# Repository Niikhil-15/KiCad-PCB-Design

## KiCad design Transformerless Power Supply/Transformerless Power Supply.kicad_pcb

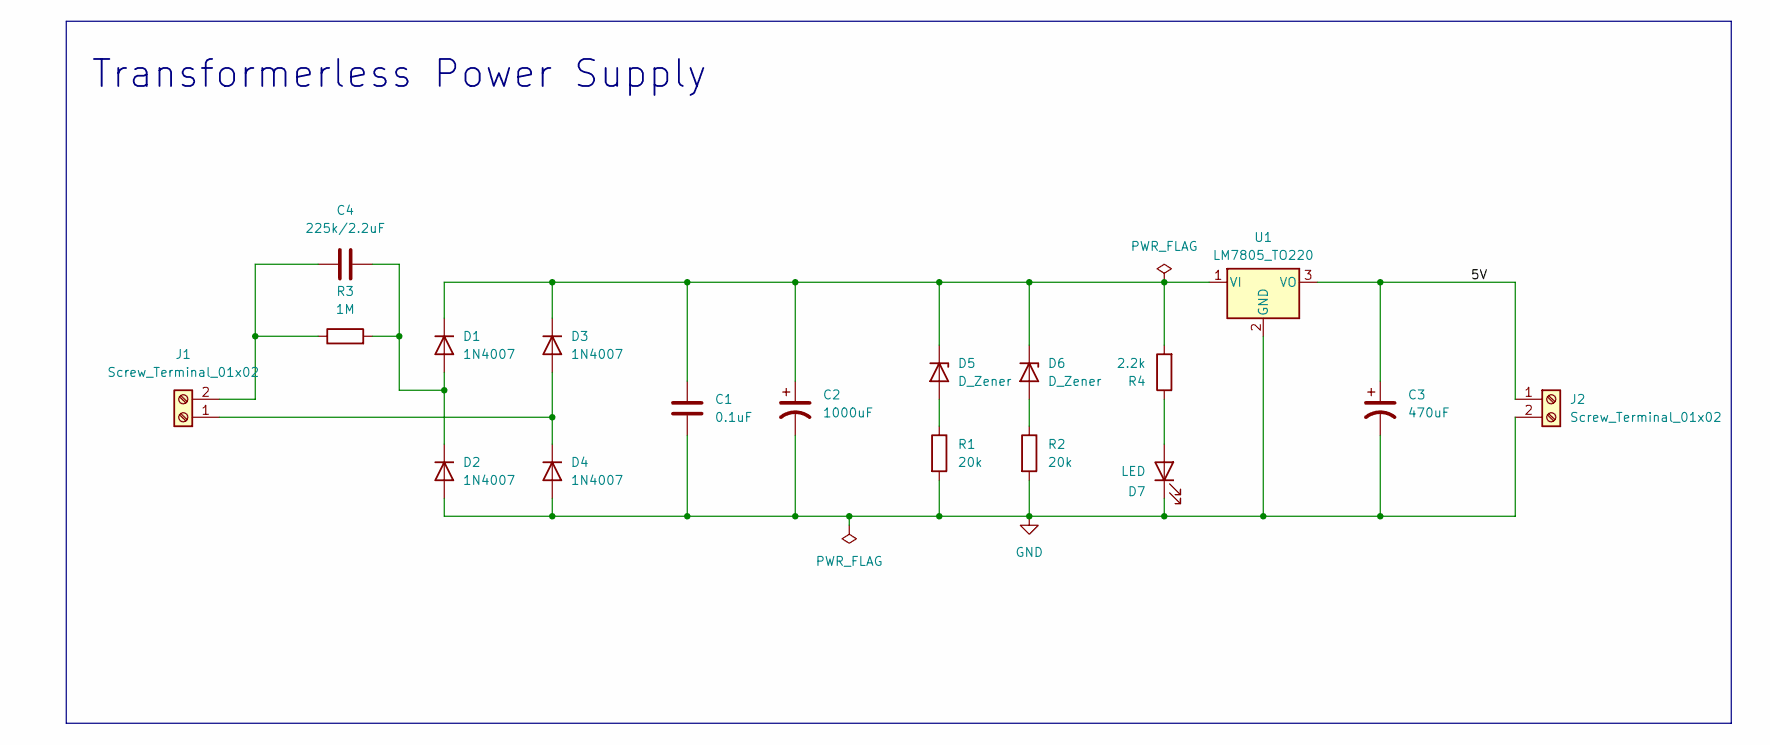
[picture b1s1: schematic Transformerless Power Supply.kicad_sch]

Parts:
C1: 0.1uF; C_Disc_D5.0mm_W2.5mm_P5.00mm
C2: 1000uF; CP_Radial_D12.5mm_P7.50mm
C3: 470uF; CP_Radial_D10.0mm_P2.50mm
C4: 225k/2.2uF; C_Rect_L9.0mm_W3.3mm_P7.50mm_MKT
D1, D2, D3, D4: 1N4007; D_DO-41_SOD81_P10.16mm_Horizontal
D5, D6: D_Zener; D_DO-34_SOD68_P7.62mm_Horizontal
D7: LED; LED_D5.0mm
J1, J2: Screw_Terminal_01x02; TerminalBlock_MaiXu_MX126-5.0-02P_1x02_P5.00mm
R1, R2: 20k; R_Axial_DIN0207_L6.3mm_D2.5mm_P7.62mm_Horizontal
R3: 1M; R_Axial_DIN0207_L6.3mm_D2.5mm_P7.62mm_Horizontal
R4: 2.2k; R_Axial_DIN0207_L6.3mm_D2.5mm_P7.62mm_Horizontal
U1: LM7805_TO220; TO-220-3_Vertical

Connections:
/5V: C3.1, J2.1, U1.3 (VO)
GND: C1.2, C2.2, C3.2, D2.2 (A), D4.2 (A), D7.1 (K), J2.2, R1.2, R2.2, U1.2 (GND)
unnamed: C4.2, D1.2 (A), D2.1 (K), R3.2
unnamed: C1.1, C2.1, D1.1 (K), D3.1 (K), D5.1 (K), D6.1 (K), R4.2, U1.1 (VI)
unnamed: D3.2 (A), D4.1 (K), J1.1
unnamed: D5.2 (A), R1.1
unnamed: D6.2 (A), R2.1
unnamed: D7.2 (A), R4.1
unnamed: C4.1, J1.2, R3.1

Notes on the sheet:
Transformerless Power Supply

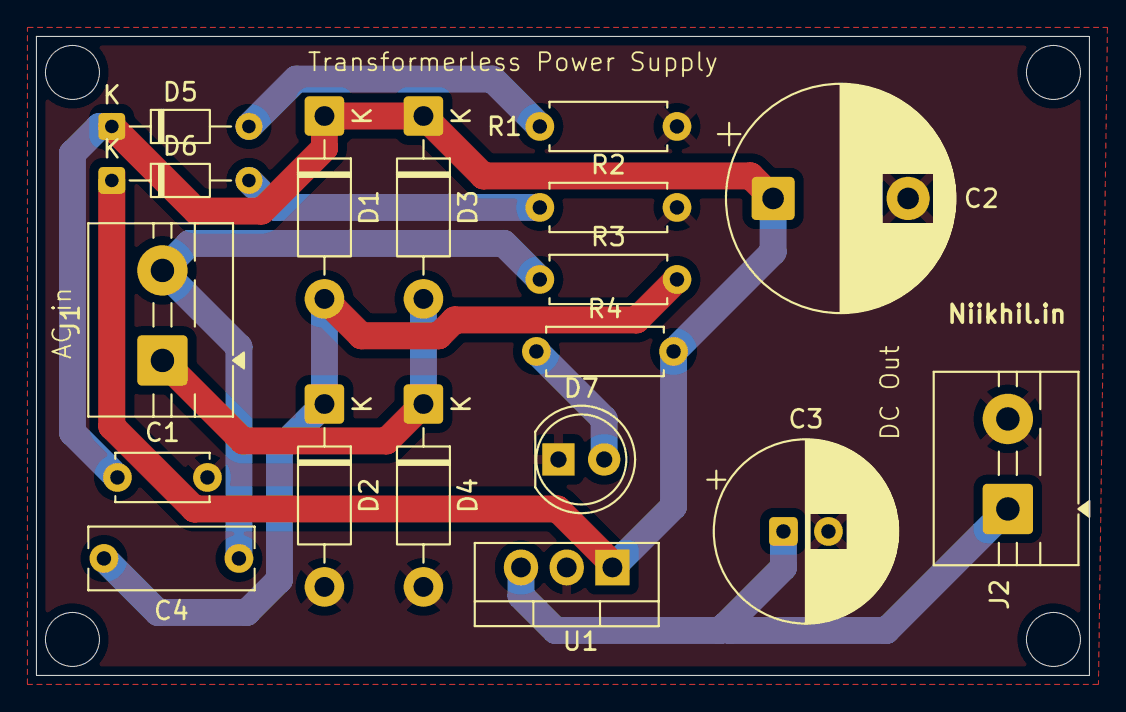
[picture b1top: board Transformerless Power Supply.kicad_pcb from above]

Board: 2 copper layers, 58.5 x 35.5 mm, 18 parts (0 on the bottom side), 9 nets.

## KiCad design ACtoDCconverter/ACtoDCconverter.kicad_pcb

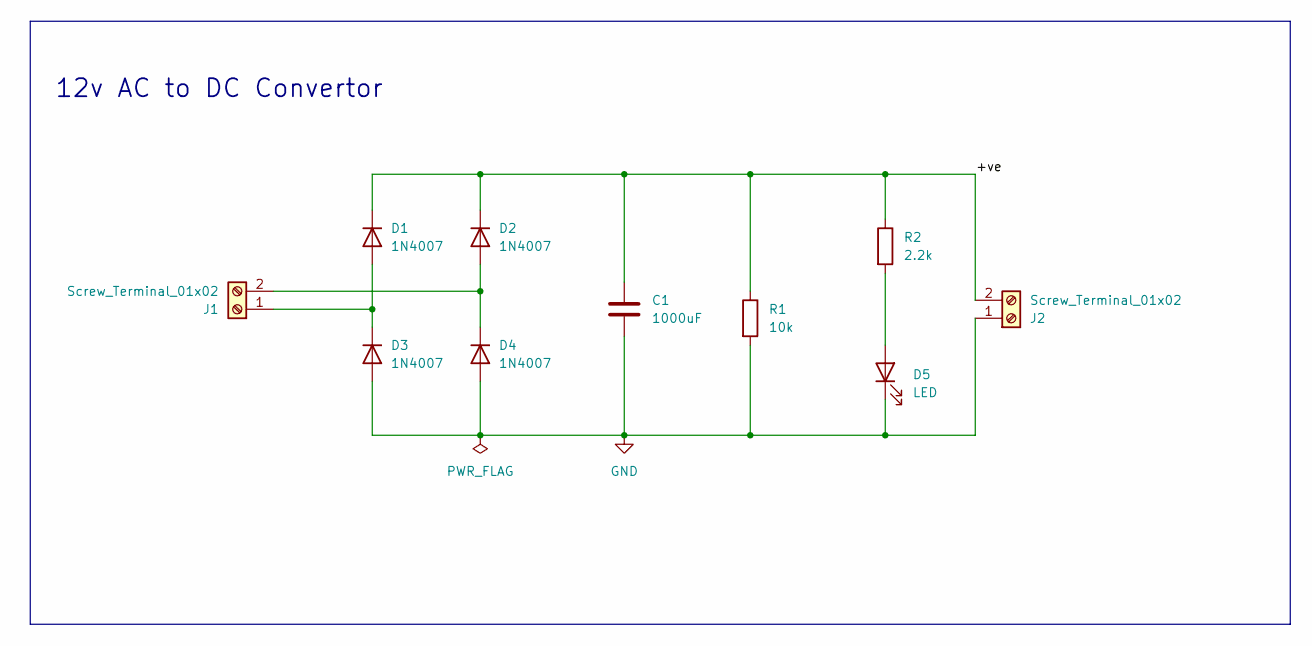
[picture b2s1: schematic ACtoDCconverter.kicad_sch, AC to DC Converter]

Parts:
C1: 1000uF; CP_Radial_D8.0mm_P5.00mm
D1, D2, D3, D4: 1N4007; D_DO-41_SOD81_P10.16mm_Horizontal
D5: LED; LED_D5.0mm
J1, J2: Screw_Terminal_01x02; TerminalBlock_MaiXu_MX126-5.0-02P_1x02_P5.00mm
R1: 10k; R_Axial_DIN0207_L6.3mm_D2.5mm_P15.24mm_Horizontal
R2: 2.2k; R_Axial_DIN0207_L6.3mm_D2.5mm_P15.24mm_Horizontal

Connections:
/+ve: C1.1, D1.1 (K), D2.1 (K), J2.2, R1.1, R2.1
GND: C1.2, D3.2 (A), D4.2 (A), D5.1 (K), J2.1, R1.2
unnamed: D1.2 (A), D3.1 (K), J1.1
unnamed: D2.2 (A), D4.1 (K), J1.2
unnamed: D5.2 (A), R2.2

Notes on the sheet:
12v AC to DC Convertor

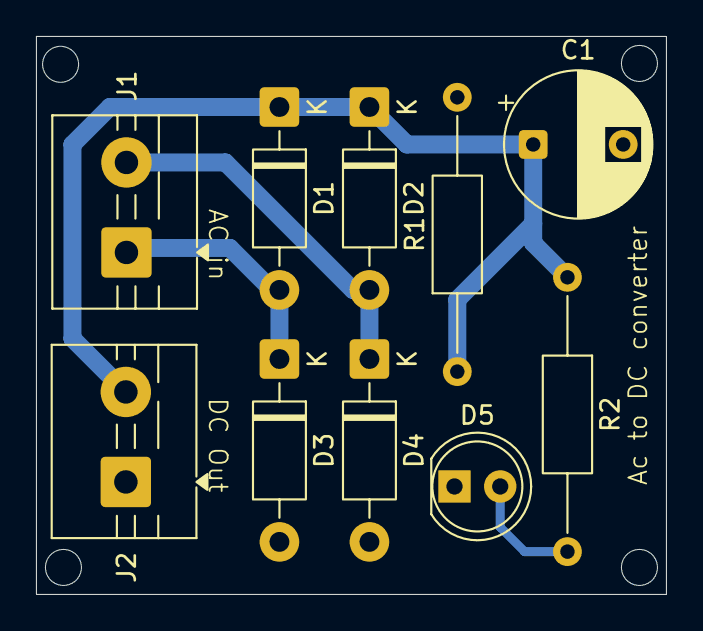
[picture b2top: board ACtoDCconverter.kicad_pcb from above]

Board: 2 copper layers, 35.0 x 31.0 mm, 10 parts (0 on the bottom side), 5 nets.

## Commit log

2026-05-24 added kicad_sch.lck in gitignore
2026-05-24 Change in gitignore file
2026-05-26 Transformerless Power Supply
